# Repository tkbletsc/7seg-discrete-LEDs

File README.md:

# 7seg-discrete-LEDs
EAGLE design for a chainable 7-segment display, plus materials to 3D print a light mask for it

See http://discspace.org/generating-3d-printable-pieces-directly-from-eagle-pcb-designs for details.

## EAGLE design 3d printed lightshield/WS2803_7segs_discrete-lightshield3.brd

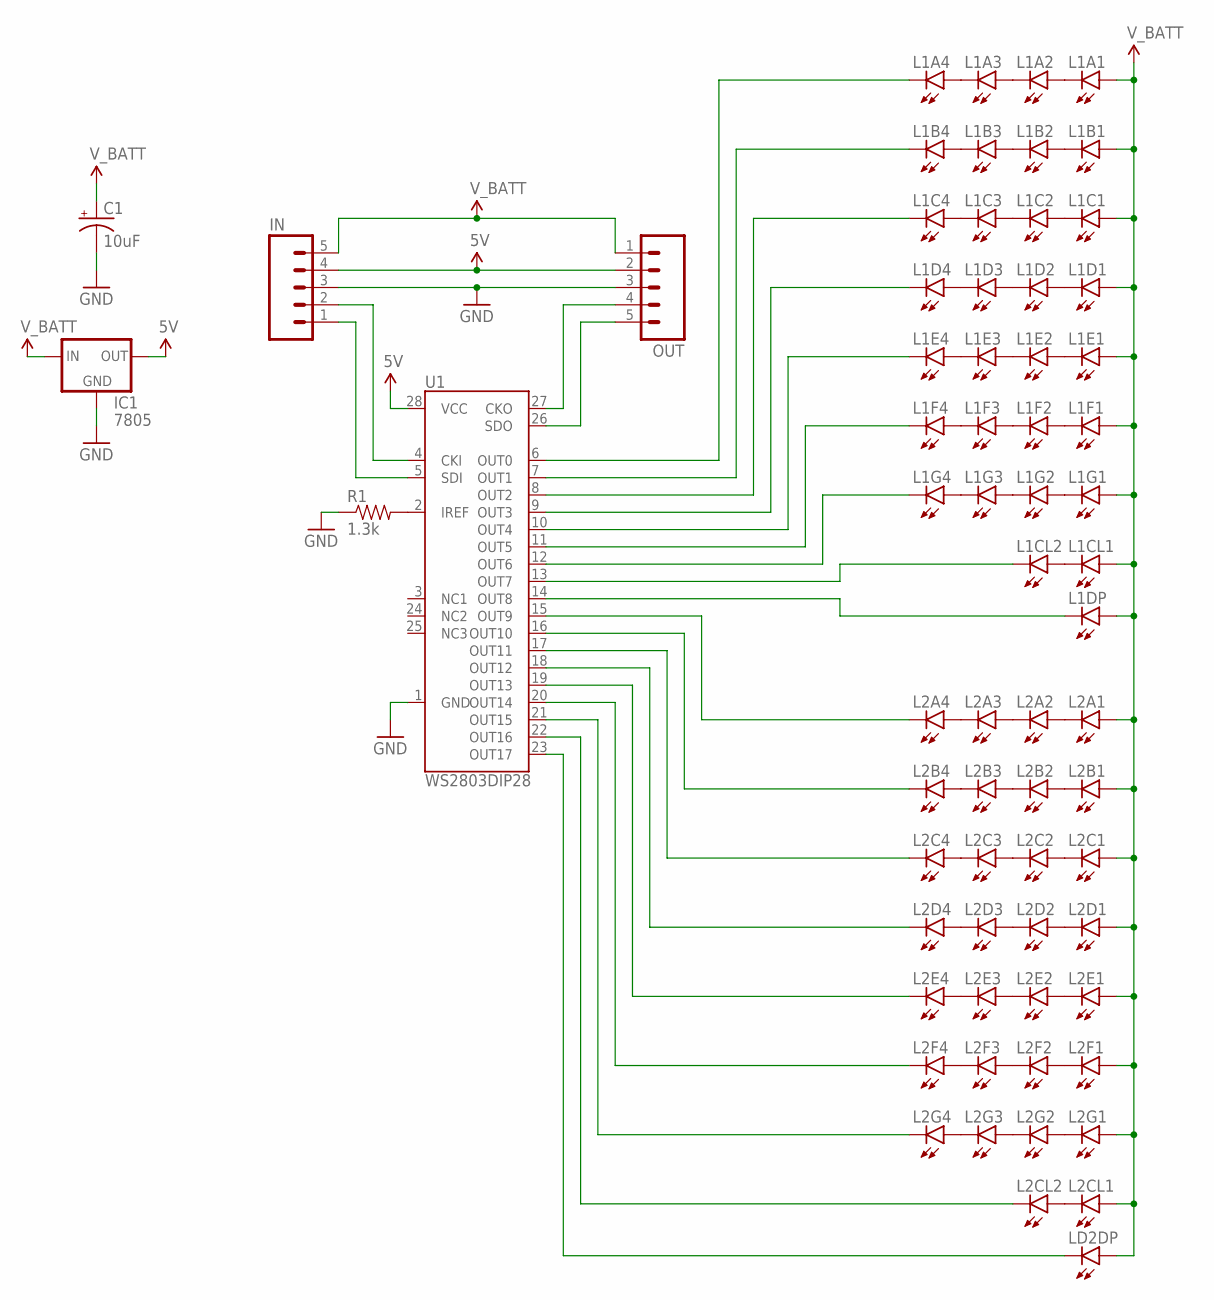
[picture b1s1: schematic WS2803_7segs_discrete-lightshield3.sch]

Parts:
C1: 10uF; CPOL-RADIAL-10UF-25V
IC1: 7805; TO-92
IN: M05PTH; 1X05
L1A1, L1A2, L1A3, L1A4, L1B1, L1B2, L1B3, L1B4, L1C1, L1C2, L1C3, L1C4, L1CL1, L1CL2, L1D1, L1D2, L1D3, L1D4, L1DP, L1E1, L1E2, L1E3, L1E4, L1F1, L1F2, L1F3, L1F4, L1G1, L1G2, L1G3, L1G4, L2A1, L2A2, L2A3, L2A4, L2B1, L2B2, L2B3, L2B4, L2C1, L2C2, L2C3, L2C4, L2CL1, L2CL2, L2D1, L2D2, L2D3, L2D4, L2E1, L2E2, L2E3, L2E4, L2F1, L2F2, L2F3, L2F4, L2G1, L2G2, L2G3, L2G4: LED5MM
LD2DP: LED5MM
OUT: M05PTH; 1X05
R1: 1.3k; AXIAL-0.4
U1: WS2803DIP28; DIP28

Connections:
5V: IC1.1 (OUT), IN.4, OUT.2, U1.28 (VCC)
GND: C1.2 (-), IC1.2 (GND), IN.3, OUT.3, R1.P$1 (1), U1.1 (GND)
unnamed: IN.2, U1.4 (CKI)
unnamed: IN.1, U1.5 (SDI)
unnamed: OUT.4, U1.27 (CKO)
unnamed: OUT.5, U1.26 (SDO)
unnamed: L1A4.K (C), U1.6 (OUT0)
unnamed: L1B4.K (C), U1.7 (OUT1)
unnamed: L1C4.K (C), U1.8 (OUT2)
unnamed: L1D4.K (C), U1.9 (OUT3)
unnamed: L1E4.K (C), U1.10 (OUT4)
unnamed: L1F4.K (C), U1.11 (OUT5)
unnamed: L1G4.K (C), U1.12 (OUT6)
unnamed: L1CL2.K (C), U1.13 (OUT7)
unnamed: L1DP.K (C), U1.14 (OUT8)
unnamed: LD2DP.K (C), U1.23 (OUT17)
unnamed: L2CL2.K (C), U1.22 (OUT16)
unnamed: L2G4.K (C), U1.21 (OUT15)
unnamed: L2F4.K (C), U1.20 (OUT14)
unnamed: L2E4.K (C), U1.19 (OUT13)
unnamed: L2D4.K (C), U1.18 (OUT12)
unnamed: L2C4.K (C), U1.17 (OUT11)
unnamed: R1.P$2 (2), U1.2 (IREF)
unnamed: L1A1.K (C), L1A2.A
unnamed: L1A2.K (C), L1A3.A
unnamed: L1A3.K (C), L1A4.A
unnamed: L1B1.K (C), L1B2.A
unnamed: L1B2.K (C), L1B3.A
unnamed: L1B3.K (C), L1B4.A
unnamed: L1C1.K (C), L1C2.A
unnamed: L1C2.K (C), L1C3.A
unnamed: L1C3.K (C), L1C4.A
unnamed: L1D1.K (C), L1D2.A
unnamed: L1D2.K (C), L1D3.A
unnamed: L1D3.K (C), L1D4.A
unnamed: L1E1.K (C), L1E2.A
unnamed: L1E2.K (C), L1E3.A
unnamed: L1E3.K (C), L1E4.A
unnamed: L1F1.K (C), L1F2.A
unnamed: L1F2.K (C), L1F3.A
unnamed: L1F3.K (C), L1F4.A
unnamed: L1G1.K (C), L1G2.A
unnamed: L1G2.K (C), L1G3.A
unnamed: L1G3.K (C), L1G4.A
unnamed: L1CL1.K (C), L1CL2.A
unnamed: L2B4.K (C), U1.16 (OUT10)
unnamed: L2A4.K (C), U1.15 (OUT9)
unnamed: L2A1.K (C), L2A2.A
unnamed: L2A2.K (C), L2A3.A
unnamed: L2A3.K (C), L2A4.A
unnamed: L2B1.K (C), L2B2.A
unnamed: L2B2.K (C), L2B3.A
unnamed: L2B3.K (C), L2B4.A
unnamed: L2C1.K (C), L2C2.A
unnamed: L2C2.K (C), L2C3.A
unnamed: L2C3.K (C), L2C4.A
unnamed: L2D1.K (C), L2D2.A
unnamed: L2D2.K (C), L2D3.A
unnamed: L2D3.K (C), L2D4.A
unnamed: L2E1.K (C), L2E2.A
unnamed: L2E2.K (C), L2E3.A
unnamed: L2E3.K (C), L2E4.A
unnamed: L2F1.K (C), L2F2.A
unnamed: L2F2.K (C), L2F3.A
unnamed: L2F3.K (C), L2F4.A
unnamed: L2G1.K (C), L2G2.A
unnamed: L2G2.K (C), L2G3.A
unnamed: L2G3.K (C), L2G4.A
unnamed: L2CL1.K (C), L2CL2.A
V_BATT: C1.1 (+), IC1.3 (IN), IN.5, L1A1.A, L1B1.A, L1C1.A, L1CL1.A, L1D1.A, L1DP.A, L1E1.A, L1F1.A, L1G1.A, L2A1.A, L2B1.A, L2C1.A, L2CL1.A, L2D1.A, L2E1.A, L2F1.A, L2G1.A, LD2DP.A, OUT.1

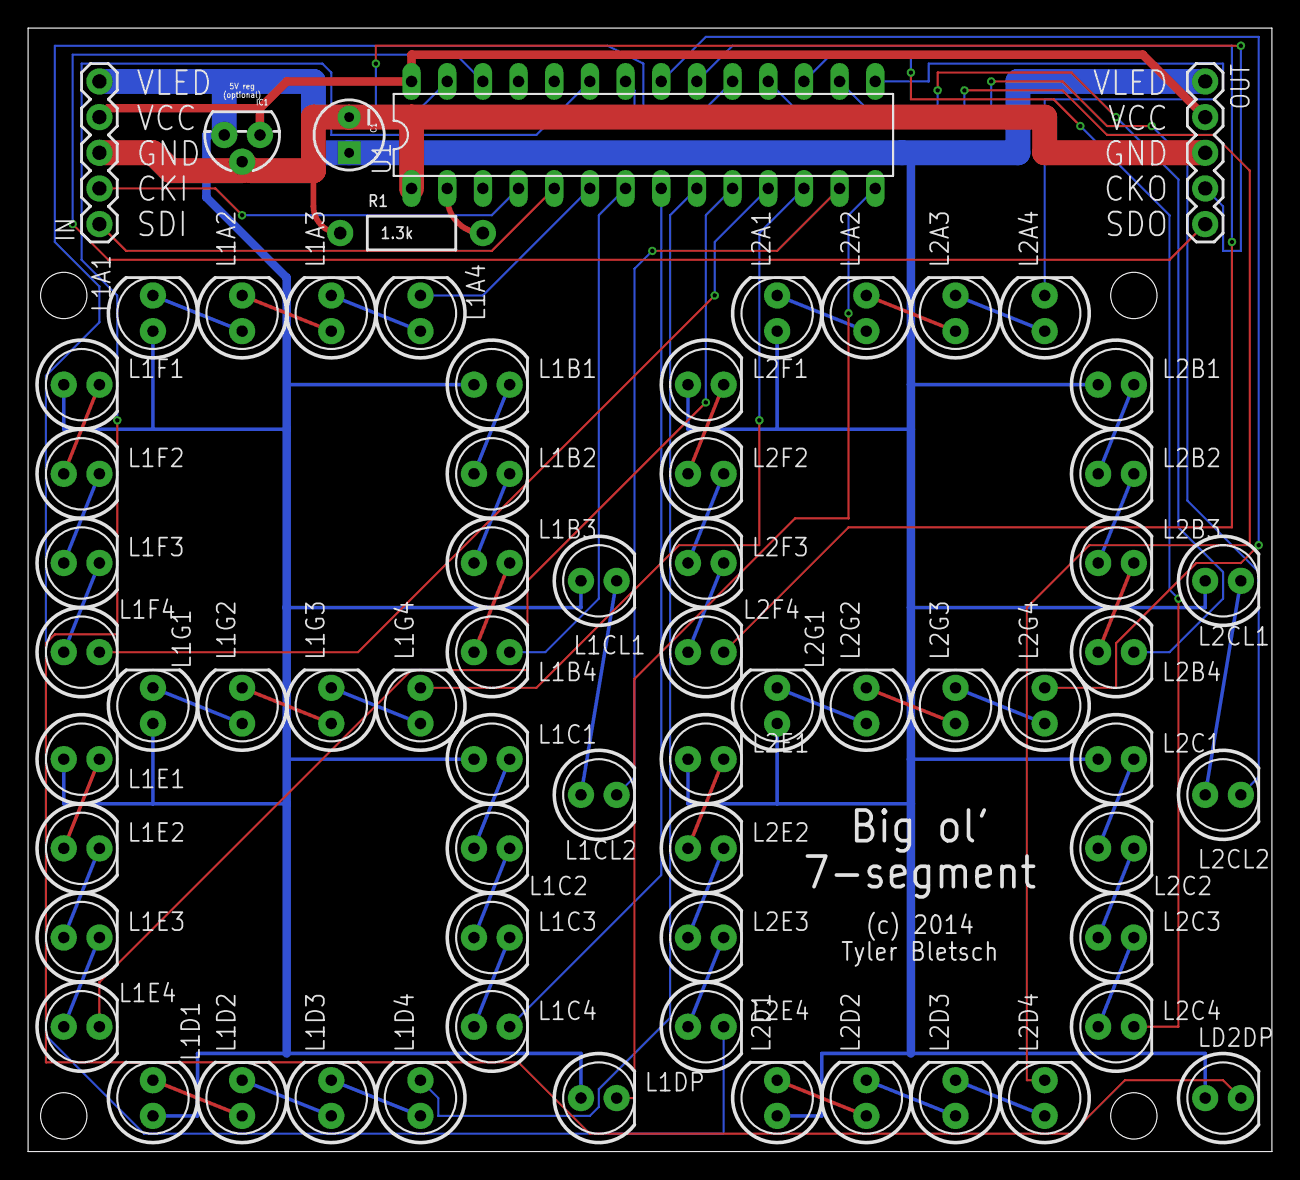
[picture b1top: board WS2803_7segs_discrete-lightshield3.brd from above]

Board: 2 copper layers, 88.6 x 80.0 mm, 68 parts (0 on the bottom side), 70 nets.

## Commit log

2015-10-25 :tada: Added .gitattributes & .gitignore files
2015-10-25 Initial import
2015-10-25 Fix minor mistake in lightmask

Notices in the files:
3d printed lightshield/WS2803_7segs_discrete-lightshield3.brd:
(c) 2014
parts and their libraries:
SparkFun-Connectors: Licensing: Creative Commons ShareAlike 4.0 International - https://creativecommons.org/licenses/by-sa/4.0
